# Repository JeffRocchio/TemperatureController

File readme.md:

# Temperature Controller

## Purpose

A relatively simple controller that can be used for both a small wood dryer and a bread proofer. Suitable for cases where temperature can vary by 1-2 degrees from the set point and where up to about 500 watts of heating element power is sufficient. For my uses one to two incandescent lights bulbs will be the heating element. The limitation on heating element power draw is really just based on the SSR used, it's heat management, and sizing of the mains wiring. In my case I am using a SSR rated at 25 amps; but no heat sink, which is why I am limiting it to 500 watts. For my uses 1-2 incandescent lights bulbs will be the heating element.

## Physical Architecture

Device is based on an ATTiny 84a MCU chip and a Solid State Relay for controlling the heater element load.

The user sets the desired temperature by use of a potentiometer. There are three LEDs that provide very basic status information on the current temperature relative to the set-point.

## Software Architecture

Probably the only significant thing to note here is that the software is structured as a mini real-time-OS (RTOS). The main program loop calls the necessary 'tasks' continuously and with no hard-coded delays. Each task is assigned a time, in milliseconds, that defines the tempo at which it should actually execute. When the task is called (from the main loop) it checks to see if it is time for it to run itself. If not, it simply returns without running any of it's logic.

The other thing to be aware of is that this application does consist of multiple files. The status LEDs are managed by their own object class, which is contained in it's own .h and .cpp file. If the software is enhanced additional class may be developed and they will also be placed in their own class files.

## Status

As of December 6, 2025 I have the controller built on only a breadboard and am testing it's operation by using a cardboard box with the light bulb heat source under it.

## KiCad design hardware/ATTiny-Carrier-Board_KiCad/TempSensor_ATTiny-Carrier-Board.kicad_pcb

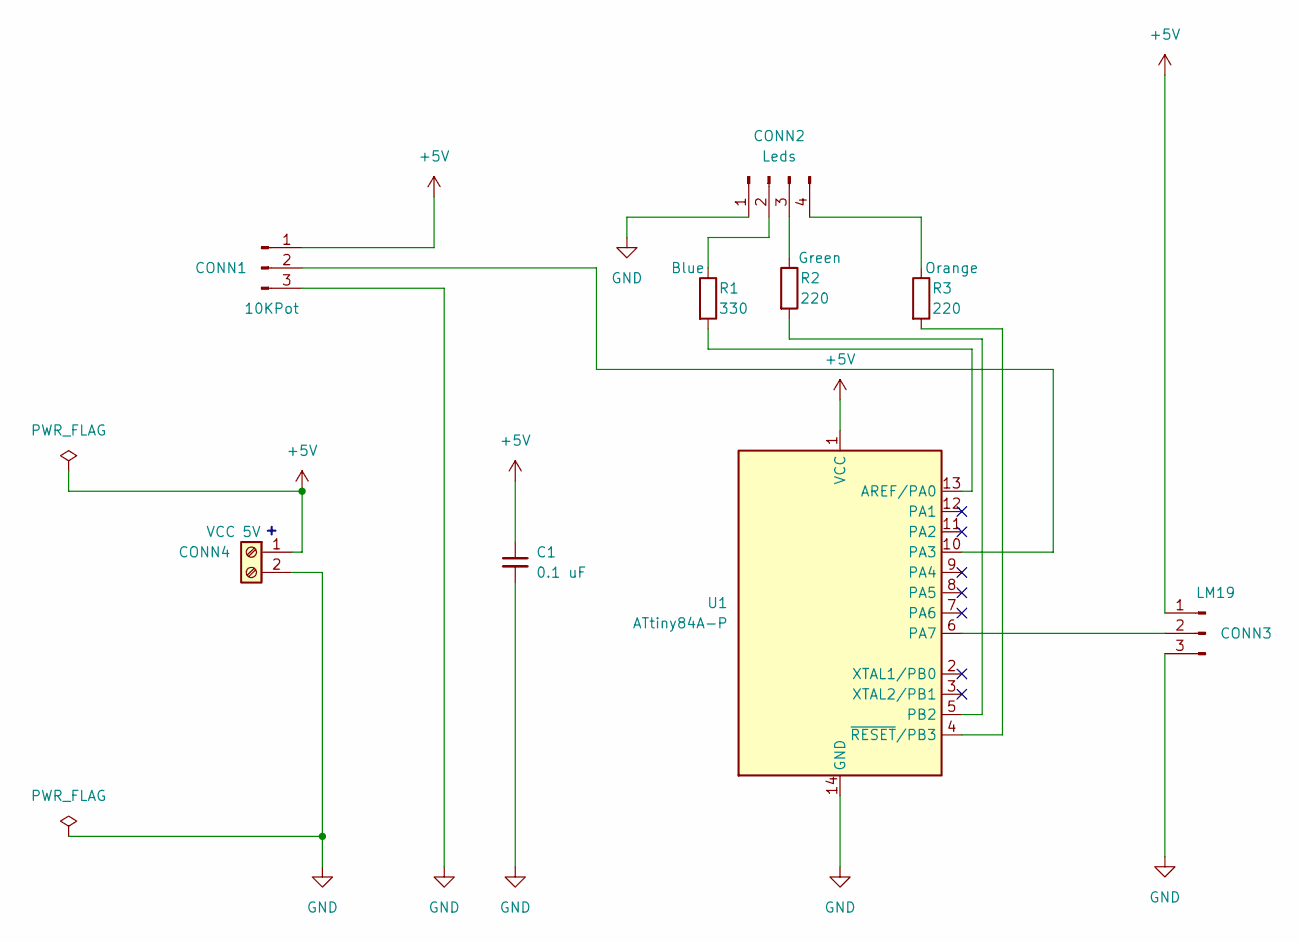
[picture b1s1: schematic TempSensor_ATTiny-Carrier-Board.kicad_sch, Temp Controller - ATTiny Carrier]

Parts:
C1: 0.1 uF; C_Disc_D3.0mm_W2.0mm_P2.50mm
CONN1, CONN3: Conn_01x03_Pin; PinHeader_1x03_P2.54mm_Vertical
CONN2: Conn_01x04_Pin; PinHeader_1x04_P2.54mm_Vertical
CONN4: 5V; TerminalBlock_Phoenix_MKDS-1,5-2-5.08_1x02_P5.08mm_Horizont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
R1: 330; R_Axial_DIN0207_L6.3mm_D2.5mm_P10.16mm_Horizontal
R2, R3: 220; R_Axial_DIN0207_L6.3mm_D2.5mm_P10.16mm_Horizontal
U1: ATtiny84A-P; DIP-14_W7.62mm

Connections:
+5V: C1.1, CONN1.1, CONN3.1, CONN4.1, U1.1 (VCC)
GND: C1.2, CONN1.3, CONN2.1, CONN3.3, CONN4.2, U1.14 (GND)
unnamed: CONN1.2, U1.10 (PA3)
unnamed: CONN2.2, R1.1
unnamed: CONN2.3, R2.1
unnamed: CONN2.4, R3.1
unnamed: CONN3.2, U1.6 (PA7)
unnamed: R1.2, U1.13 (AREF/PA0)
unnamed: R2.2, U1.5 (PB2)
unnamed: R3.2, U1.4 (~RESET/PB3)

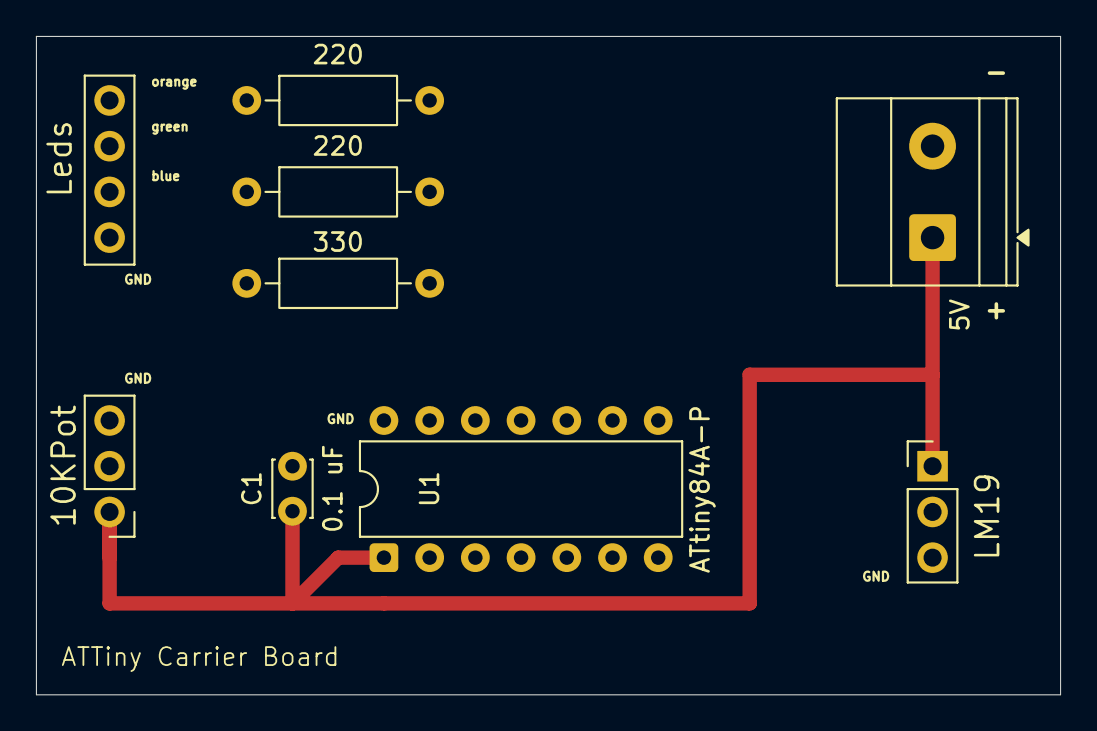
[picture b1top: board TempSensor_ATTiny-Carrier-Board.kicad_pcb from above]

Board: 12 copper layers, 56.9 x 36.6 mm, 9 parts (0 on the bottom side), 10 nets.

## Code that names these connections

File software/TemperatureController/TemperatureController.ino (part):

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// ---------------- Digital Pin Assignments -----------------------------------
const uint8_t SSR_PIN         = PIN_PB0;  // physical pin  2 - SSR control (digital)
const uint8_t LED_ABOVE_PIN   = PIN_PB1;  // physical pin  3 - status LED
const uint8_t LED_INBAND_PIN  = PIN_PB2;  // physical pin  5 - status LED
const uint8_t LED_BELOW_PIN   = PIN_PA0;  // physical pin 13 - status LED

// ---------------- Analog Pin Assignments: using Ax form for ADC -------------
const uint8_t TEMP_PIN  = A7;       // PA7, physical pin 6 - LM19 Vout
const uint8_t POT_PIN   = A3;       // PA3, physical pin 10 - pot wiper

// ---------------- LM19 Constants --------------------------------------------
const float VREF        = 5.0;
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
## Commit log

2025-12-07 Initializing git with first completed proof-of-concept
2025-12-07 Added some images of the POC build
2025-12-22 Updated .gitignore
2025-12-22 Working breadboard prototype
